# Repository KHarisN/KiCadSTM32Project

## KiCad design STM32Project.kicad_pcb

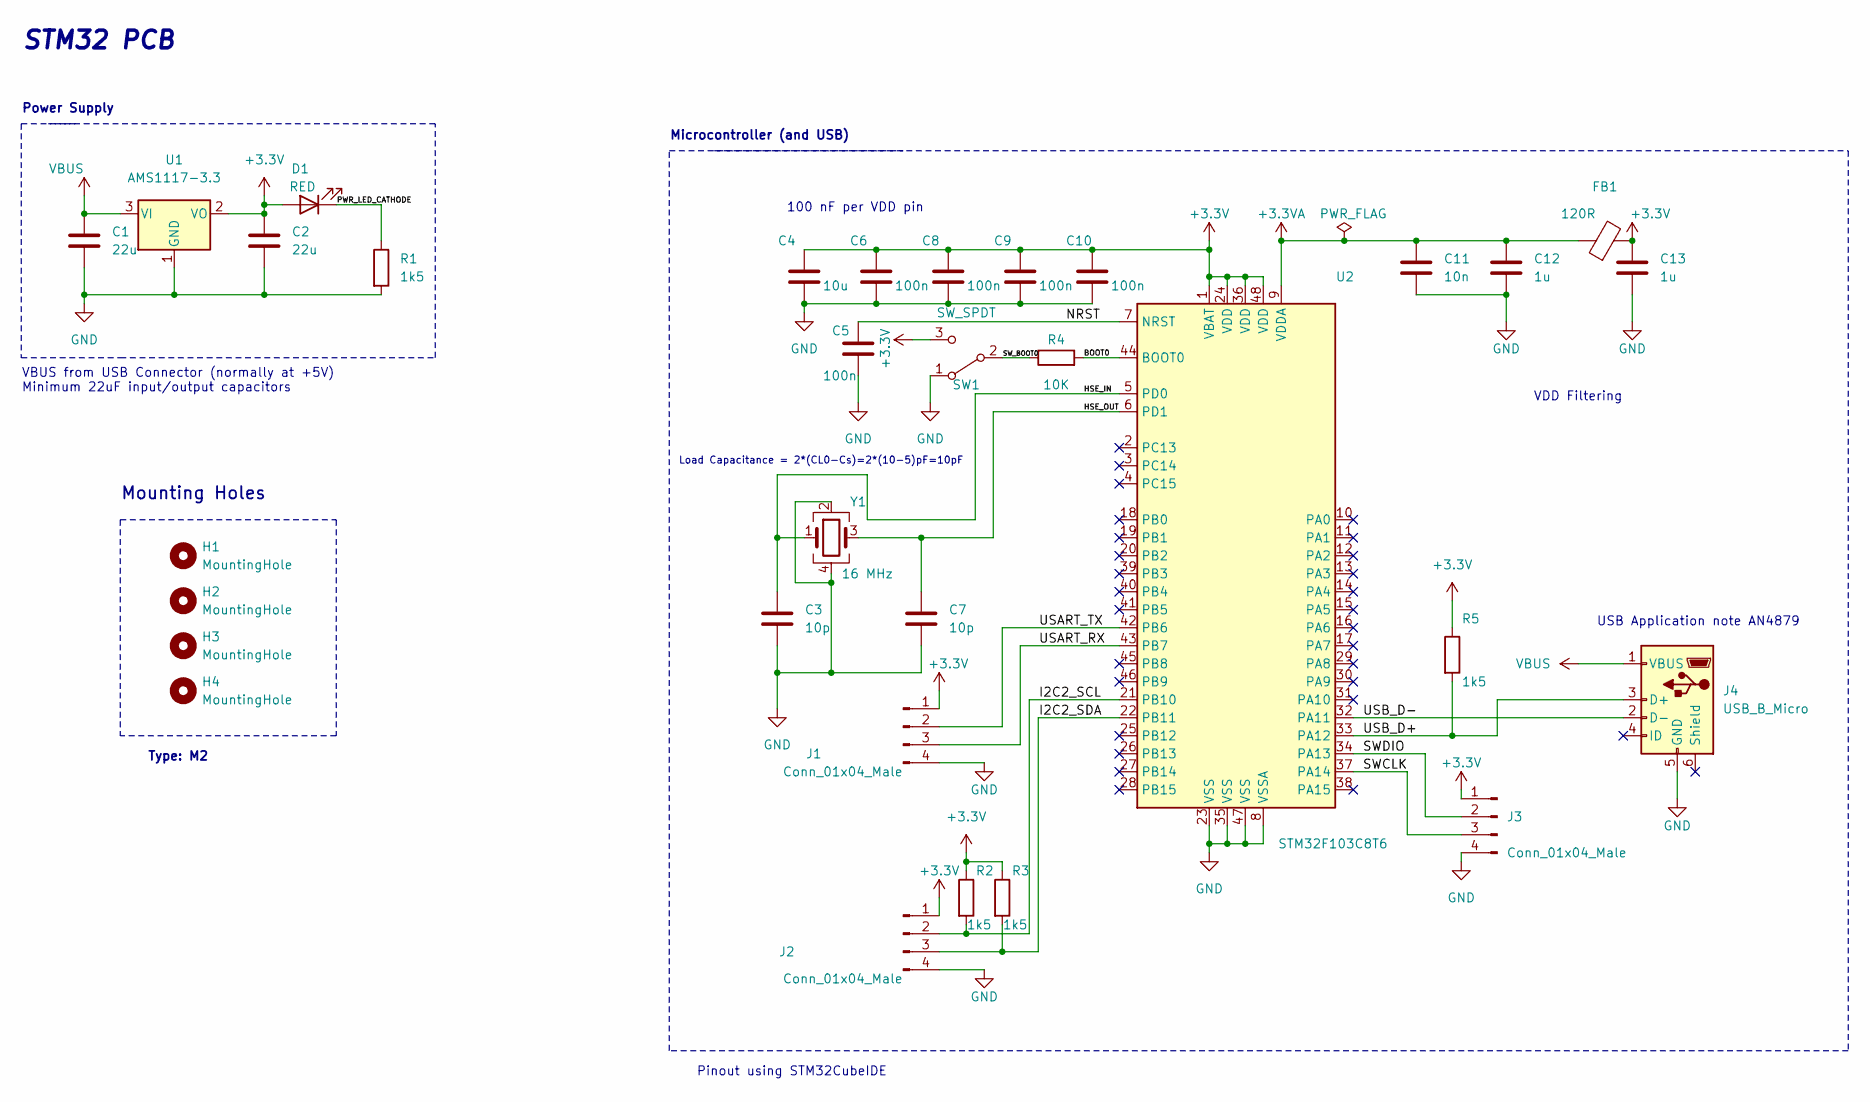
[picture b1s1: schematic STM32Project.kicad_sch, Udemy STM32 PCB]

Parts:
C1, C2: 22u; C_0805_2012Metric
C3, C7: 10p; C_0402_1005Metric
C4: 10u; C_0603_1608Metric
C5, C6, C8, C9, C10: 100n; C_0402_1005Metric
C11: 10n; C_0402_1005Metric
C12, C13: 1u; C_0402_1005Metric
D1: RED; LED_0603_1608Metric
FB1: 120R; L_0603_1608Metric
H1, H2, H3, H4: MountingHole; MountingHole_2.2mm_M2
J1, J2, J3: Conn_01x04_Male; PinHeader_1x04_P2.54mm_Vertical
J4: USB_B_Micro; USB_Micro-B_Wuerth_629105150521
R1, R2, R3, R5: 1k5; R_0402_1005Metric
R4: 10K; R_0402_1005Metric
SW1: SW_SPDT; SW_SPDT_PCM12
U1: AMS1117-3.3; SOT-223-3_TabPin2
U2: STM32F103C8T6; LQFP-48_7x7mm_P0.5mm
Y1: 16 MHz; Crystal_SMD_3225-4Pin_3.2x2.5mm

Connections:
+3.3V: C2.1, C4.1, C6.1, C8.1, C9.1, C10.1, C13.1, D1.2 (A), FB1.2, J1.1, J2.1, J3.1, R2.1, R3.1, R5.1, SW1.3 (C), U1.2 (VO), U2.1 (VBAT), U2.24 (VDD), U2.36 (VDD), U2.48 (VDD)
+3.3VA: C11.1, C12.1, FB1.1, U2.9 (VDDA)
/BOOT0: R4.2, U2.44 (BOOT0)
/HSE_IN: C3.1, U2.5 (PD0), Y1.1
/HSE_OUT: C7.1, U2.6 (PD1), Y1.3
/I2C2_SCL: J2.2, R2.2, U2.21 (PB10)
/I2C2_SDA: J2.3, R3.2, U2.22 (PB11)
/NRST: C5.1, U2.7 (NRST)
/PWR_LED_CATHODE: D1.1 (K), R1.1
/SWCLK: J3.3, U2.37 (PA14)
/SWDIO: J3.2, U2.34 (PA13)
/SW_BOOT0: R4.1, SW1.2 (B)
/USART_RX: J1.3, U2.43 (PB7)
/USART_TX: J1.2, U2.42 (PB6)
/USB_D+: J4.3 (D+), R5.2, U2.33 (PA12)
/USB_D-: J4.2 (D-), U2.32 (PA11)
GND: C1.2, C2.2, C3.2, C4.2, C5.2, C6.2, C7.2, C8.2, C9.2, C10.2, C11.2, C12.2, C13.2, J1.4, J2.4, J3.4, J4.5 (GND), R1.2, SW1.1 (A), U1.1 (GND), U2.8 (VSSA), U2.23 (VSS), U2.35 (VSS), U2.47 (VSS), Y1.2, Y1.4
VBUS: C1.1, J4.1 (VBUS), U1.3 (VI)

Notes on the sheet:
Pinout using STM32CubeIDE
STM32 PCB
Microcontroller (and USB)
Mounting Holes
USB Application note AN4879
VBUS from USB Connector (normally at +5V) Minimum 22uF input/output capacitors
100 nF per VDD pin
VDD Filtering
Power Supply
Type: M2
Load Capacitance = 2*(CL0-Cs)=2*(10-5)pF=10pF

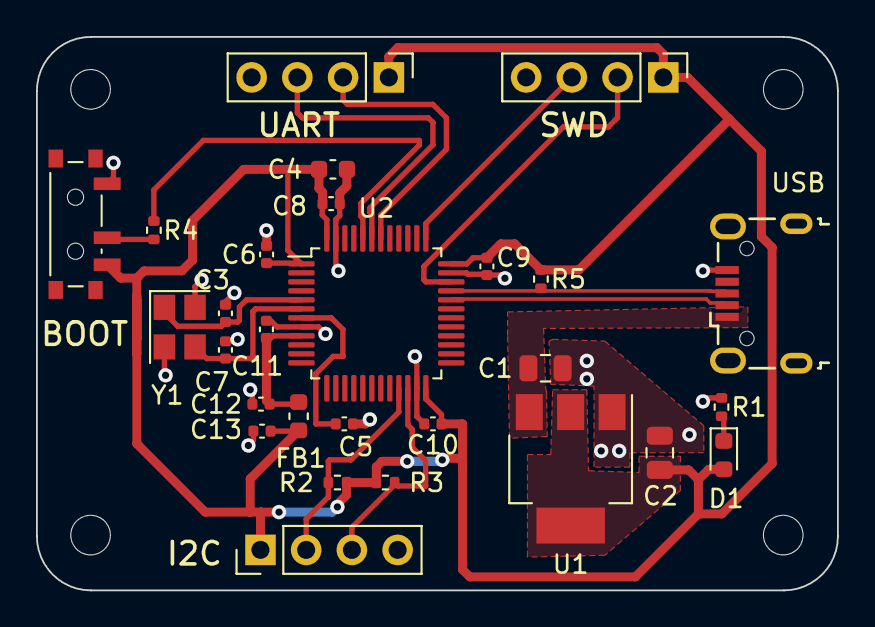
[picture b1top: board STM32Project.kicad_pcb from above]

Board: 2 copper layers, 44.5 x 30.8 mm, 32 parts (0 on the bottom side), 18 nets.
